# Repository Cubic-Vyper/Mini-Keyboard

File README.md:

# Mini-Keyboard
This is a tiny keyboard

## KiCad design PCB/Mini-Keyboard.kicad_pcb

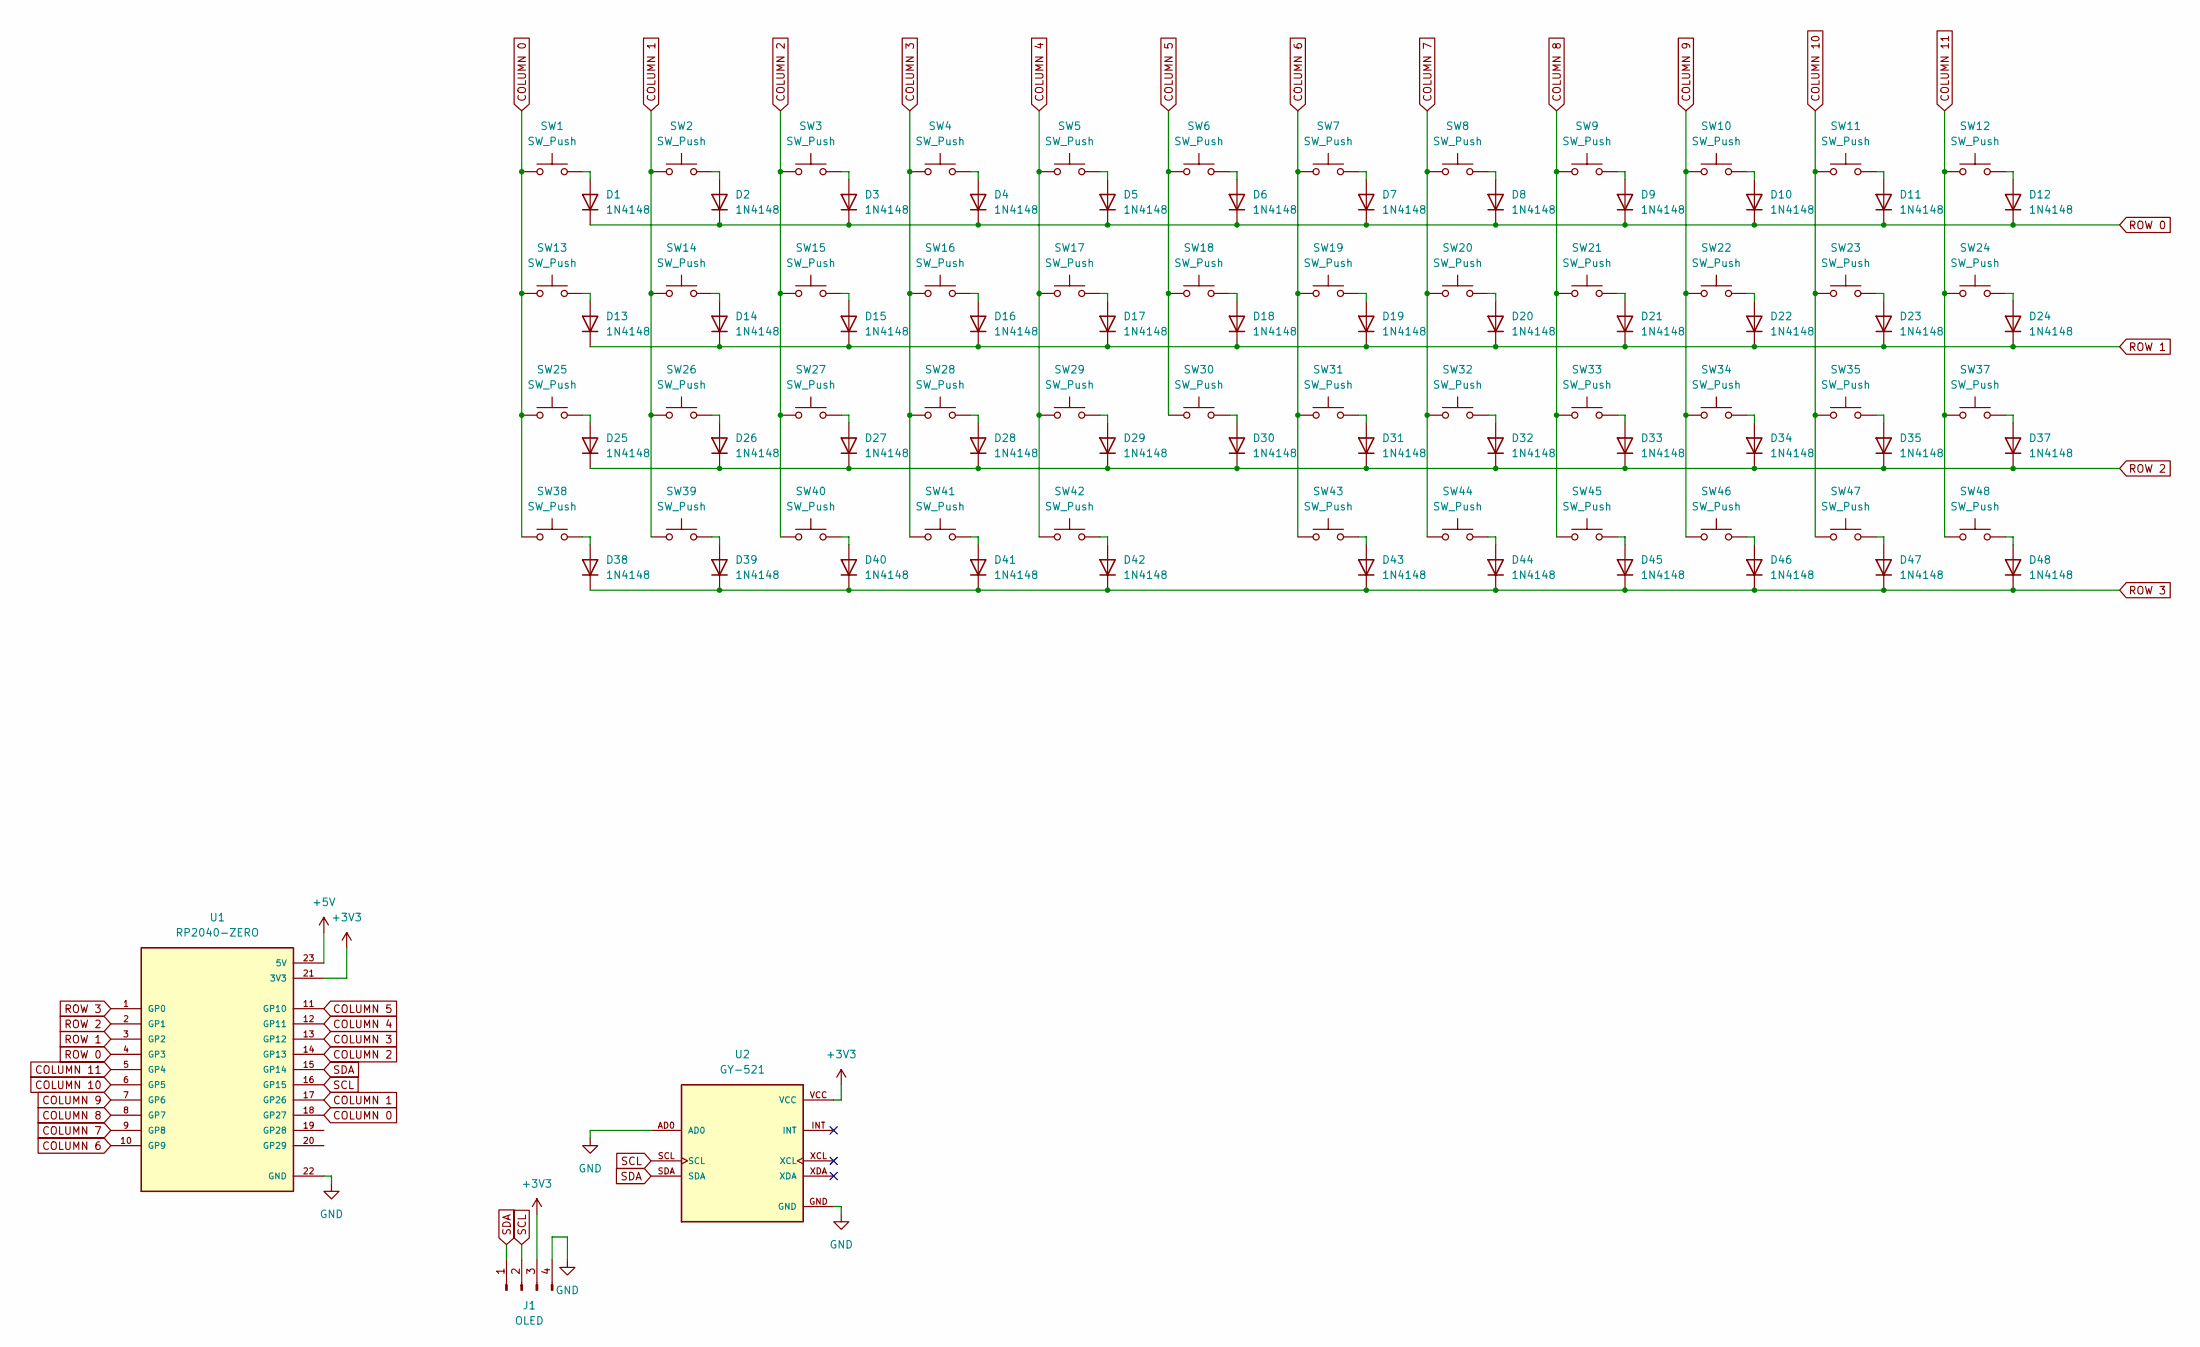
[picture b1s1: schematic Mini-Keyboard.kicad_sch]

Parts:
D1, D2, D3, D4, D5, D6, D7, D8, D9, D10, D11, D12, D13, D14, D15, D16, D17, D18, D19, D20, D21, D22, D23, D24, D25, D26, D27, D28, D29, D30, D31, D32, D33, D34, D35, D37, D38, D39, D40, D41, D42, D43, D44, D45, D46, D47, D48: 1N4148; D_DO-35_SOD27_P7.62mm_Horizontal
J1: OLED; 0.91 OLED ☻
SW1, SW2, SW3, SW4, SW5, SW6, SW7, SW8, SW9, SW10, SW11, SW12, SW13, SW14, SW15, SW16, SW17, SW18, SW19, SW20, SW21, SW22, SW23, SW24, SW25, SW26, SW27, SW28, SW29, SW30, SW31, SW32, SW33, SW34, SW35, SW37, SW38, SW39, SW40, SW41, SW42, SW43, SW44, SW45, SW46, SW47, SW48: SW_Push; SW_PUSH_6mm_H4.3mm
U1: RP2040-ZERO; MODULE_RP2040-ZERO; PARTREV NA
U2: GY-521; MODULE_GY-521; PARTREV NA

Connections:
+3V3: J1.3, U1.21 (3V3), U2.VCC
+5V: U1.23 (5V)
COLUMN 0: SW1.1, SW13.1, SW25.1, SW38.1, U1.18 (GP27)
COLUMN 1: SW2.1, SW14.1, SW26.1, SW39.1, U1.17 (GP26)
COLUMN 2: SW3.1, SW15.1, SW27.1, SW40.1, U1.14 (GP13)
COLUMN 3: SW4.1, SW16.1, SW28.1, SW41.1, U1.13 (GP12)
COLUMN 4: SW5.1, SW17.1, SW29.1, SW42.1, U1.12 (GP11)
COLUMN 5: SW6.1, SW18.1, SW30.1, U1.11 (GP10)
COLUMN 6: SW7.1, SW19.1, SW31.1, SW43.1, U1.10 (GP9)
COLUMN 7: SW8.1, SW20.1, SW32.1, SW44.1, U1.9 (GP8)
COLUMN 8: SW9.1, SW21.1, SW33.1, SW45.1, U1.8 (GP7)
COLUMN 9: SW10.1, SW22.1, SW34.1, SW46.1, U1.7 (GP6)
COLUMN 10: SW11.1, SW23.1, SW35.1, SW47.1, U1.6 (GP5)
COLUMN 11: SW12.1, SW24.1, SW37.1, SW48.1, U1.5 (GP4)
GND: J1.4, U1.22 (GND), U2.AD0, U2.GND
unnamed: D1.2 (A), SW1.2
unnamed: D2.2 (A), SW2.2
unnamed: D3.2 (A), SW3.2
unnamed: D4.2 (A), SW4.2
unnamed: D5.2 (A), SW5.2
unnamed: D6.2 (A), SW6.2
unnamed: D7.2 (A), SW7.2
unnamed: D8.2 (A), SW8.2
unnamed: D9.2 (A), SW9.2
unnamed: D10.2 (A), SW10.2
unnamed: D11.2 (A), SW11.2
unnamed: D12.2 (A), SW12.2
unnamed: D13.2 (A), SW13.2
unnamed: D14.2 (A), SW14.2
unnamed: D15.2 (A), SW15.2
unnamed: D16.2 (A), SW16.2
unnamed: D17.2 (A), SW17.2
unnamed: D18.2 (A), SW18.2
unnamed: D19.2 (A), SW19.2
unnamed: D20.2 (A), SW20.2
unnamed: D21.2 (A), SW21.2
unnamed: D22.2 (A), SW22.2
unnamed: D23.2 (A), SW23.2
unnamed: D24.2 (A), SW24.2
unnamed: D25.2 (A), SW25.2
unnamed: D26.2 (A), SW26.2
unnamed: D27.2 (A), SW27.2
unnamed: D28.2 (A), SW28.2
unnamed: D29.2 (A), SW29.2
unnamed: D30.2 (A), SW30.2
unnamed: D31.2 (A), SW31.2
unnamed: D32.2 (A), SW32.2
unnamed: D33.2 (A), SW33.2
unnamed: D34.2 (A), SW34.2
unnamed: D35.2 (A), SW35.2
unnamed: D37.2 (A), SW37.2
unnamed: D38.2 (A), SW38.2
unnamed: D39.2 (A), SW39.2
unnamed: D40.2 (A), SW40.2
unnamed: D41.2 (A), SW41.2
unnamed: D42.2 (A), SW42.2
unnamed: D43.2 (A), SW43.2
unnamed: D44.2 (A), SW44.2
unnamed: D45.2 (A), SW45.2
unnamed: D46.2 (A), SW46.2
unnamed: D47.2 (A), SW47.2
unnamed: D48.2 (A), SW48.2
ROW 0: D1.1 (K), D2.1 (K), D3.1 (K), D4.1 (K), D5.1 (K), D6.1 (K), D7.1 (K), D8.1 (K), D9.1 (K), D10.1 (K), D11.1 (K), D12.1 (K), U1.4 (GP3)
ROW 1: D13.1 (K), D14.1 (K), D15.1 (K), D16.1 (K), D17.1 (K), D18.1 (K), D19.1 (K), D20.1 (K), D21.1 (K), D22.1 (K), D23.1 (K), D24.1 (K), U1.3 (GP2)
ROW 2: D25.1 (K), D26.1 (K), D27.1 (K), D28.1 (K), D29.1 (K), D30.1 (K), D31.1 (K), D32.1 (K), D33.1 (K), D34.1 (K), D35.1 (K), D37.1 (K), U1.2 (GP1)
ROW 3: D38.1 (K), D39.1 (K), D40.1 (K), D41.1 (K), D42.1 (K), D43.1 (K), D44.1 (K), D45.1 (K), D46.1 (K), D47.1 (K), D48.1 (K), U1.1 (GP0)
SCL: J1.2, U1.16 (GP15), U2.SCL
SDA: J1.1, U1.15 (GP14), U2.SDA

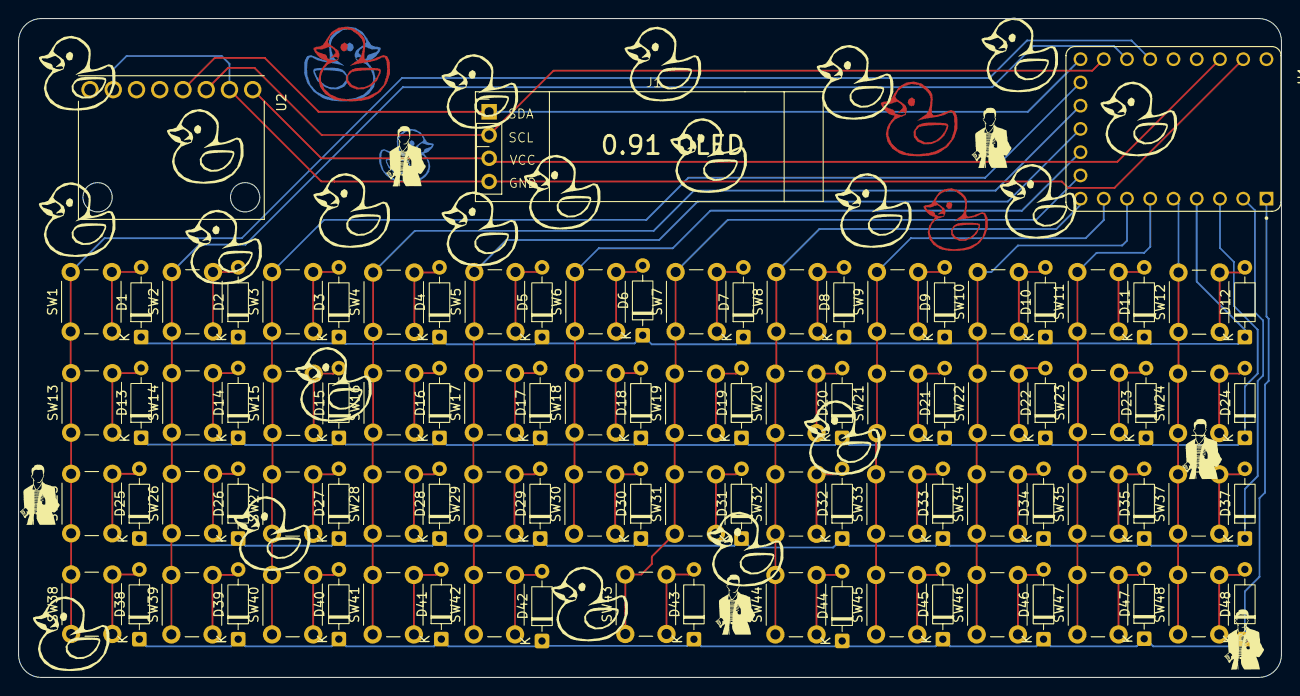
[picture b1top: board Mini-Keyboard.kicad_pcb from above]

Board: 2 copper layers, 138.0 x 72.0 mm, 97 parts (0 on the bottom side), 67 nets.

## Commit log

2026-06-28 Create delete
